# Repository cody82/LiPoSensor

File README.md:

# LiPoSensor
This is a Li-Poly voltage sensor that connects to Frsky receivers or to flight controllers that
support one of the Frsky telemetry protocols.
This repository includes the Arduino source code and the KiCad PCB.

# Compiling
You need Arduino >= 1.6.

# Board
*WARNING: DO NOT POWER THE BOARD FROM BOTH LIPO AND RECEIVER AS IT MIGHT CATCH FIRE*

You need KiCad >= 4.0 to edit the PCB.

You can order the PCB from OSH Park:

<a href="https://oshpark.com/shared_projects/UHJ9S4BJ"></img></a>

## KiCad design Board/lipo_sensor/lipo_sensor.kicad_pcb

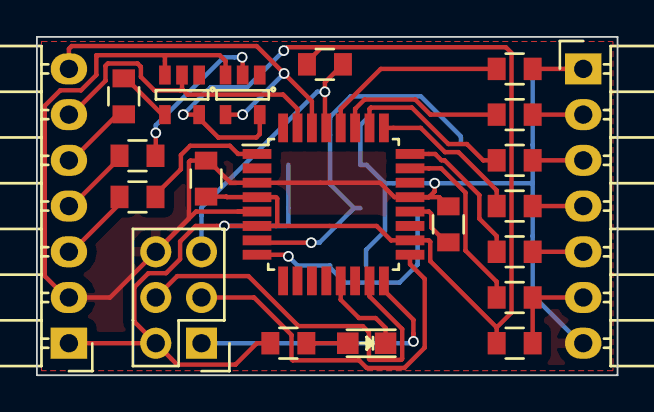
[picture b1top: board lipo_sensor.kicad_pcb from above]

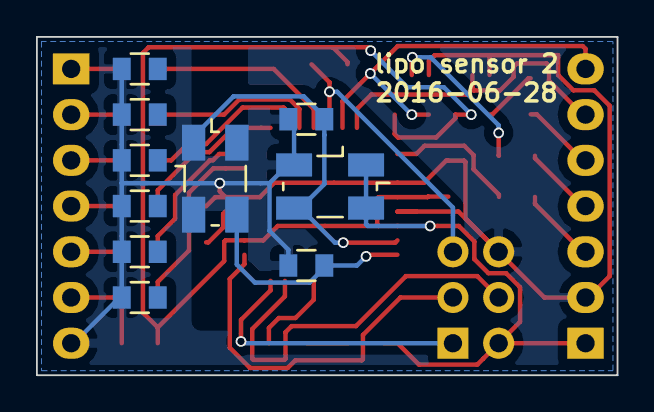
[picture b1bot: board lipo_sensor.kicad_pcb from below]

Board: 2 copper layers, 32.3 x 18.8 mm, 31 parts (10 on the bottom side), 31 nets.

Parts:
5k1: 4k7; C_0805
C1, C3: 100nF; C_0805
C2, C5: 22pF; C_0805
D1: LED; LED_0805
IC1: ATMEGA328P-A; TQFP-32_7x7mm_Pitch0.8mm
P1: CONN_02X03; Pin_Header_Straight_2x03
P2, P3: CONN_01X07; Pin_Header_Angled_1x07
P4: OSZILLATOR; Oszillator_SMD_5032_4Pads
P5, P6: INVERTER; SOT-23-5
P7: QUARZ; Oszillator_SMD_5032_4Pads
R1: 680; C_0805
R2, R5, R9: 22k; C_0805
R3, R6: 1k; C_0805
R4: 0; C_0805
R7: 18k; C_0805
R8: 1k2; C_0805
R10: 1k8; C_0805
R11: 15k; C_0805
R12: 2k2; C_0805
R13: 12k; C_0805
R14: 3k9; C_0805
R15, R17: R; C_0805
R16: 10k; C_0805

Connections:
/Cell1: IC1.23, R13.2, R14.1
/Cell2: IC1.24, R11.2, R12.1
/Cell3: IC1.25, R9.2, R10.1
/Cell4: IC1.26, R7.2, R8.1
/Cell5: IC1.27, R5.2, R6.1
/Cell6: IC1.28, R2.2, R3.1
/LED: D1.1, IC1.13
/RX: IC1.30, P2.7, P6.4
/S.Port: 5k1.2, IC1.1
/TX: IC1.31, P2.6, P5.2
GND: C1.2, C2.1, C3.1, C5.1, IC1.3, IC1.5, IC1.21, P1.6, P2.2, P3.7, P4.2, P5.3, P6.3, R3.2, R6.2, R8.2, R10.2, R12.2, R14.2
unnamed: 5k1.1, P2.3
unnamed: C2.2, IC1.7, P4.3, P7.1
unnamed: C3.2, IC1.20
unnamed: C5.2, IC1.8, P7.3
unnamed: D1.2, R1.2
unnamed: IC1.15, P1.4
unnamed: IC1.16, P1.1
unnamed: IC1.17, P1.3
unnamed: IC1.29, P1.5, R16.2
unnamed: P2.4, R17.2
unnamed: P2.5, R15.2
unnamed: P3.1, R2.1
unnamed: P3.2, R5.1
unnamed: P3.3, R7.1
unnamed: P3.4, R9.1
unnamed: P3.5, R11.1
unnamed: P3.6, R4.2, R13.1
unnamed: P5.4, R15.1
unnamed: P6.2, R17.1
VCC: C1.1, IC1.4, IC1.6, IC1.18, P1.2, P2.1, P4.1, P4.4, P5.5, P6.5, R1.1, R4.1, R16.1

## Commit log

2016-06-17 Arduino wants it like that.
2016-06-18 Add sketch for FrskyD telemetry. https://github.com/jcheger/arduino-frskyd
2016-06-18 Add VFAS to FrskyD.
2016-06-18 Add KiCad board.
2016-06-26 Shrink layout and fix oszillator connections.
2016-06-28 Fix inverted RX/TX.
2016-06-28 Replace big crystal with smaller crystal: QC5A Series 3.2x5.0 4-Pad SMD Quartz Crystal Unit
2016-06-28 Ready for order.
2016-06-28 Forgot to commit.
2016-07-01 Add HOTT support. Untested. https://github.com/chriszero/ArduHottSensor
2016-07-19 Add datasheet.
2016-07-22 Add pictures.
2016-07-27 Update pictures.
2016-07-27 Add pinout.
2017-06-05 Add FrSky Smart Port library.
2017-06-05 Add https://github.com/jcheger/arduino-frskyd library as submodule.
